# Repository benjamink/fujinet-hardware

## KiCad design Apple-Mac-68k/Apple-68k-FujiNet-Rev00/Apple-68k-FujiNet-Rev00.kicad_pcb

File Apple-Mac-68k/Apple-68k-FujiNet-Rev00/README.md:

# Apple 68k FujiNet Rev00 (ESP32-S3)

Prototype of Rev0 with the ESP32-DevKitC replaced by an ESP32-S3-DevKitC-1 (N16R8) style board,
such as the dual USB-C "HW-678" clones. Not yet built or tested.

Schematic - [Apple-68k-FujiNet-Rev00-Schematic.pdf](../docs/Apple-68k-FujiNet-Rev00-Schematic.pdf)

- The board is 15.24mm longer at the USB edge so the longer S3 devkit's USB end sits at the edge,
  as on Rev0. The Pico (with D3, JP1 and R1-R3 under it), S1, C2 and the bottom mounting holes
  moved down with it, so both USB ports stay on that edge; the case needs the same change.
- U2's right-hand header row has holes at both 22.86mm (Espressif DevKitC-1) and 25.4mm (most
  clones) spacing. Solder the socket into whichever row matches your board.
- RN1 moved to clear the 22.86mm row. Everything else is where it was on Rev0.
- Mac signals, the Pico and the microSD socket are unchanged. The GPIO assignment is new:

| Signal | GPIO | | Signal | GPIO |
|---|---|---|---|---|
| SPI_CS | 4 | | WR_DATA | 1 |
| SPI_MOSI | 5 | | WREQ | 2 |
| SPI_CLK | 6 | | ENBL2 | 42 |
| SPI_MISO | 7 | | HDSEL | 41 |
| SD_CD | 15 | | RMT_FROM_ESP | 40 |
| BUTTON_A | 16 | | PICO_RX_TO_ESP (ESP TX) | 39 |
| LED_WIFI | 17 | | PICO_TX_TO_ESP (ESP RX) | 21 |
| BUS_LED | 18 | | SAFE_RESET | 8 |

GPIO 0, 3, 45 and 46 (strapping), 19/20 (USB), 43/44 (UART0), 35-37 (octal PSRAM) and 38/48
(RGB LED on most devkits) are left unconnected.

The ESP32-S3-DevKitC symbol and footprint in `lib/` are derived from Espressif's
[kicad-libraries](https://github.com/espressif/kicad-libraries) (CC-BY-SA 4.0).

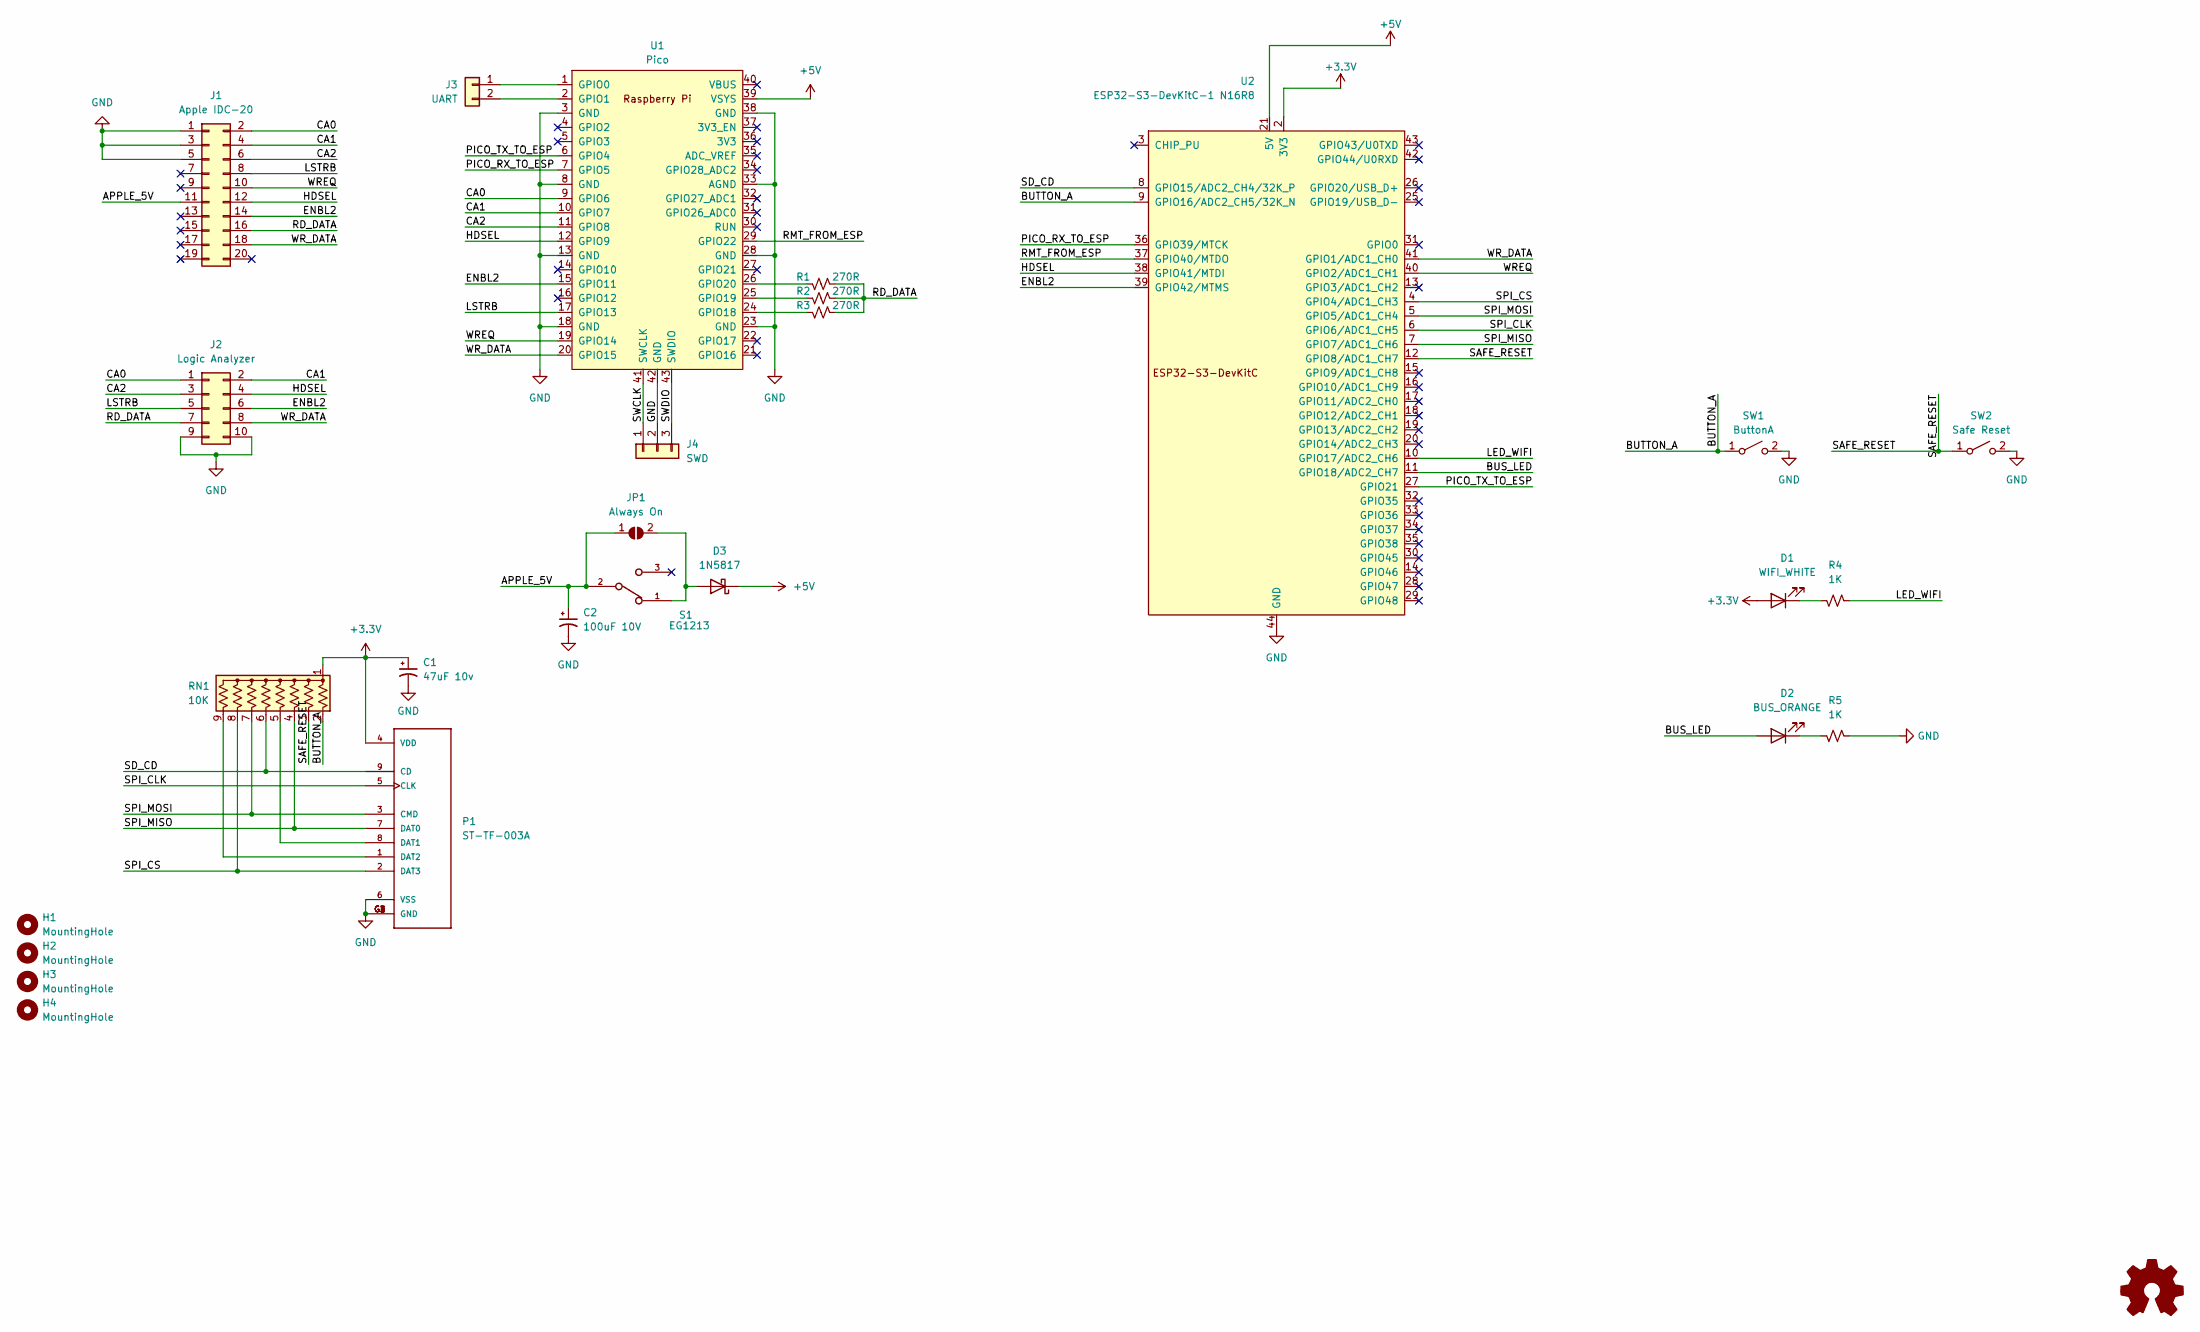
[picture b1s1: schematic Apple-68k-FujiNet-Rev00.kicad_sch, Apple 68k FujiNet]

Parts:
C1: 47uF 10v; CP_EIA-3528-15_AVX-H_Pad1.50x2.35mm_HandSolder
C2: 100uF 10V; CP_Radial_D6.3mm_P2.50mm
D1: WIFI_WHITE; LED_D5.0mm
D2: BUS_ORANGE; LED_D5.0mm
D3: 1N5817; D_DO-41_SOD81_P10.16mm_Horizontal
H1, H2, H3, H4: MountingHole; MountingHole_3.2mm_M3
J1: Apple IDC-20; IDC-Header_2x10_P2.54mm_Horizontal
J2: Logic Analyzer; PinHeader_2x05_P2.54mm_Vertical
J3: UART; PinHeader_1x02_P2.54mm_Vertical
J4: SWD; PinHeader_1x03_P2.54mm_Vertical
JP1: Always On; SolderJumper-2_P1.3mm_Open_RoundedPad1.0x1.5mm
P1: ST-TF-003A; SUNTECH_ST-TF-003A
R1, R2, R3: 270R; R_Axial_DIN0207_L6.3mm_D2.5mm_P7.62mm_Horizontal
R4, R5: 1K; R_Axial_DIN0207_L6.3mm_D2.5mm_P7.62mm_Horizontal
RN1: 10K; R_Array_SIP9
S1: EG1213; SW_EG1213
SW1: ButtonA; SW_PUSH_6mm_H5mm
SW2: Safe Reset; SW_PUSH_6mm_H5mm
U1: Pico; RPi_Pico_THT
U2: ESP32-S3-DevKitC-1 N16R8; ESP32-S3-DevKitC-1_DualRow

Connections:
+3.3V: C1.1, D1.2 (A), P1.4 (VDD), RN1.1 (common), U2.1 (3V3), U2.2 (3V3)
+5V: D3.1 (K), U1.39 (VSYS), U2.21 (5V)
/APPLE_5V: C2.1, J1.11, JP1.1 (A), S1.2
/BUS_LED: D2.2 (A), U2.11 (GPIO18/ADC2_CH7)
/BUTTON_A: RN1.2 (R1), SW1.1 (A), U2.9 (GPIO16/ADC2_CH5/32K_N)
/CA0: J1.2, J2.1, U1.9 (GPIO6)
/CA1: J1.4, J2.2, U1.10 (GPIO7)
/CA2: J1.6, J2.3, U1.11 (GPIO8)
/ENBL2: J1.14, J2.6, U1.15 (GPIO11), U2.39 (GPIO42/MTMS)
/HDSEL: J1.12, J2.4, U1.12 (GPIO9), U2.38 (GPIO41/MTDI)
/LED_WIFI: R4.2, U2.10 (GPIO17/ADC2_CH6)
/LSTRB: J1.8, J2.5, U1.17 (GPIO13)
/PICO_RX_TO_ESP: U1.7 (GPIO5), U2.36 (GPIO39/MTCK)
/PICO_TX_TO_ESP: U1.6 (GPIO4), U2.27 (GPIO21)
/RD_DATA: J1.16, J2.7, R1.2, R2.2, R3.2
/RMT_FROM_ESP: U1.29 (GPIO22), U2.37 (GPIO40/MTDO)
/SAFE_RESET: RN1.3 (R2), SW2.1 (A), U2.12 (GPIO8/ADC1_CH7)
/SD_CD: P1.9 (CD), RN1.6 (R5), U2.8 (GPIO15/ADC2_CH4/32K_P)
/SPI_CLK: P1.5 (CLK), U2.6 (GPIO6/ADC1_CH5)
/SPI_CS: P1.2 (DAT3), RN1.8 (R7), U2.4 (GPIO4/ADC1_CH3)
/SPI_MISO: P1.7 (DAT0), RN1.4 (R3), U2.7 (GPIO7/ADC1_CH6)
/SPI_MOSI: P1.3 (CMD), RN1.7 (R6), U2.5 (GPIO5/ADC1_CH4)
/SWCLK: J4.1, U1.41 (SWCLK)
/SWDIO: J4.3, U1.43 (SWDIO)
/WREQ: J1.10, U1.19 (GPIO14), U2.40 (GPIO2/ADC1_CH1)
/WR_DATA: J1.18, J2.8, U1.20 (GPIO15), U2.41 (GPIO1/ADC1_CH0)
GND: C1.2, C2.2, J1.1, J1.3, J1.5, J2.9, J2.10, J4.2, P1.6 (VSS), P1.G1 (GND), P1.G2 (GND), P1.G3 (GND), P1.G4 (GND), R5.2, SW1.2 (B), SW2.2 (B), U1.3 (GND), U1.8 (GND), U1.13 (GND), U1.18 (GND), U1.23 (GND), U1.28 (GND), U1.33 (AGND), U1.38 (GND), U1.42 (GND), U2.22 (GND), U2.23 (GND), U2.24 (GND), U2.44 (GND)
unnamed: D1.1 (K), R4.1
unnamed: D2.1 (K), R5.1
unnamed: D3.2 (A), JP1.2 (B), S1.1
unnamed: J3.1, U1.1 (GPIO0)
unnamed: J3.2, U1.2 (GPIO1)
unnamed: P1.8 (DAT1), RN1.5 (R4)
unnamed: P1.1 (DAT2), RN1.9 (R8)
unnamed: R3.1, U1.24 (GPIO18)
unnamed: R2.1, U1.25 (GPIO19)
unnamed: R1.1, U1.26 (GPIO20)

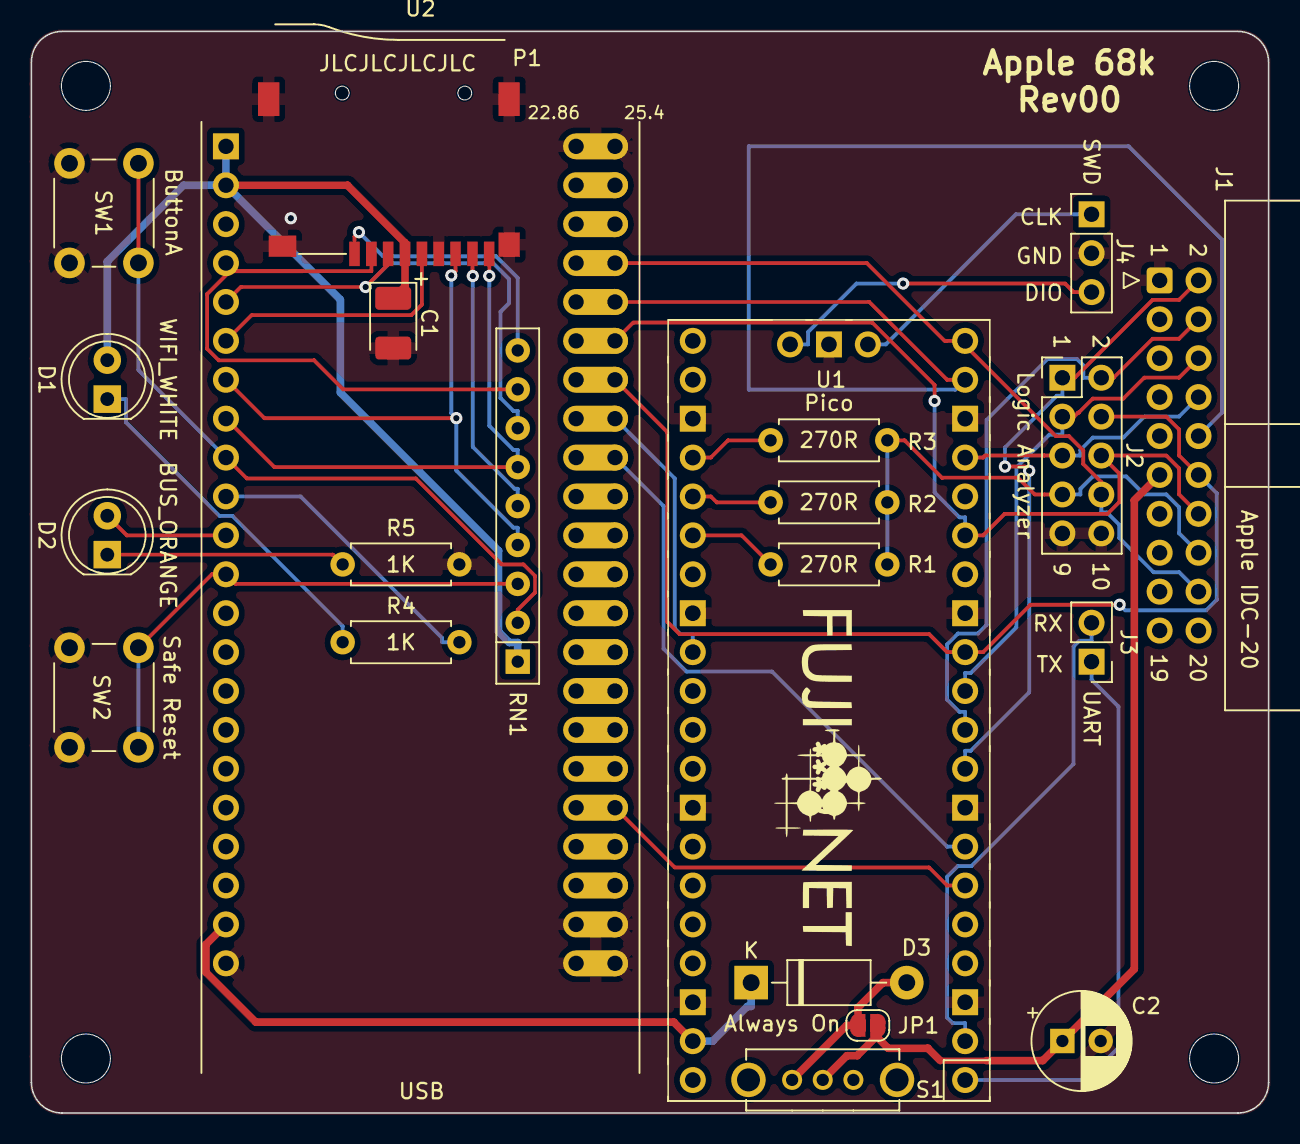
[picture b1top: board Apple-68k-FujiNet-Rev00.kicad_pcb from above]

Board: 2 copper layers, 80.8 x 70.6 mm, 26 parts (0 on the bottom side), 37 nets.

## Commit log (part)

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2025-03-03 replace level-shifter component
2025-03-03 fix some DRC errors
2025-03-03 fix U2 silk screen placement

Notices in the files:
parts and their libraries:
ESP32-S3-DevKitC-1 on 2.54mm female headers. J1 row at x=0; J3 row at both 22.86mm (Espressif) and 25.4mm (common clones) spacing. Derived from Espressif kicad-libraries ESP32-S3-DevKitC (CC-BY-SA 4.0).
